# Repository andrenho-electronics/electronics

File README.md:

# electronics
Some hobbyist electronics projects.

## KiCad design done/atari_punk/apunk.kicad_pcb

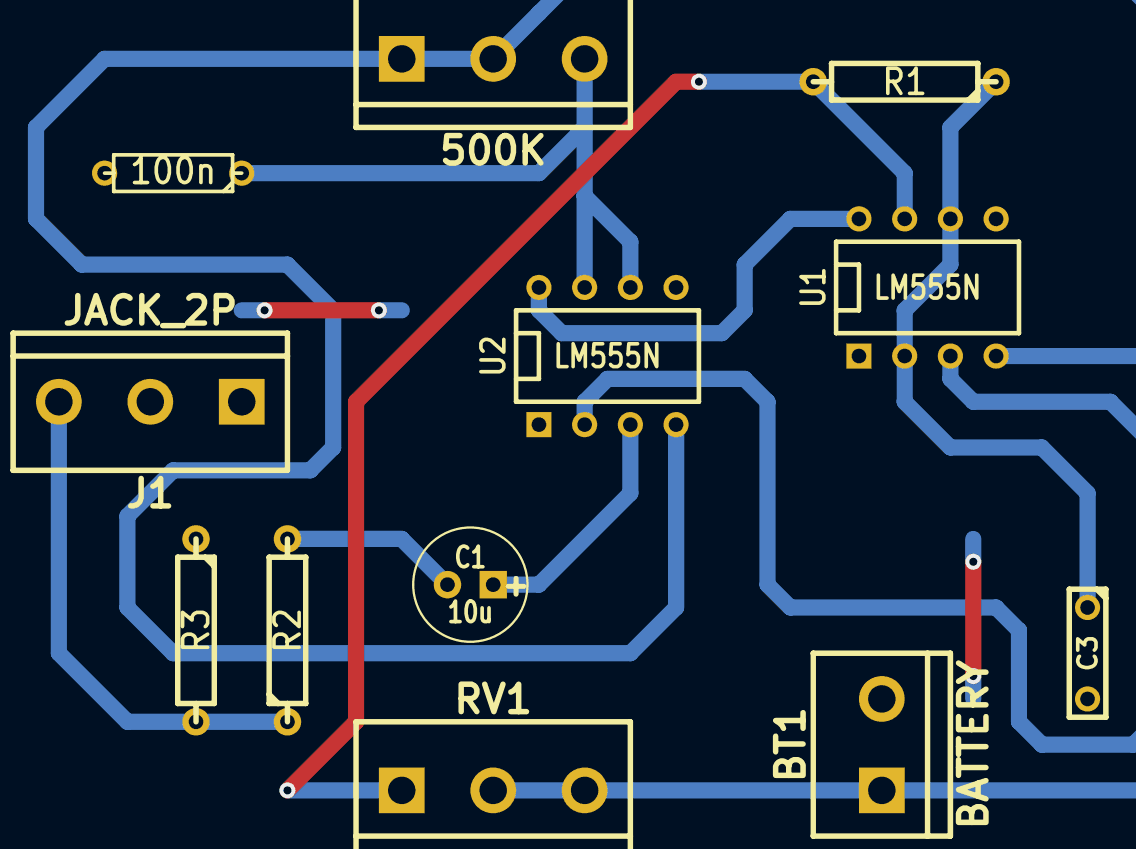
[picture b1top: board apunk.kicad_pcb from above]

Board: 2 copper layers, 12 parts (0 on the bottom side), 10 nets.

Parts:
BT1: BATTERY; bornier2
C1: 10u; C1V7
C3: 10n; C2
C4: 100n; R3
J1: JACK_2P; bornier3
R1: 1K; R4
R2: 10K; R4
R3: 6K8; R4
RV1, RV2: 500K; bornier3
U1, U2: LM555N; DIP-8__300

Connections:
+9V: BT1.1, RV1.2, RV1.3, RV2.1, RV2.2, U1.4, U2.4
GND: BT1.2, C3.2, C4.2, J1.1, J1.2, R3.1, U1.1, U2.1
unnamed: J1.3, R2.1, R3.2
unnamed: U1.3, U2.2
unnamed: R1.2, RV1.1, U1.7
unnamed: C3.1, R1.1, U1.2, U1.6
unnamed: C4.1, RV2.3, U2.6, U2.7
unnamed: C1.1, U2.3
unnamed: C1.2, R2.2
VCC: U1.8, U2.8

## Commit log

2015-11-17 First commit.
2015-11-17 Added MSX storage.
2015-12-10 Changing the buzzer layout
2015-12-24 Deleted main, created new main.
2015-12-25 Code done!
2015-12-28 New datasheets.
2015-12-31 7-segment display finished!
2016-01-01 Liquid crystal working!
2016-01-02 Led dimmer done!
2016-01-05 Added logic analyzer.
2016-01-06 Digital block done!
